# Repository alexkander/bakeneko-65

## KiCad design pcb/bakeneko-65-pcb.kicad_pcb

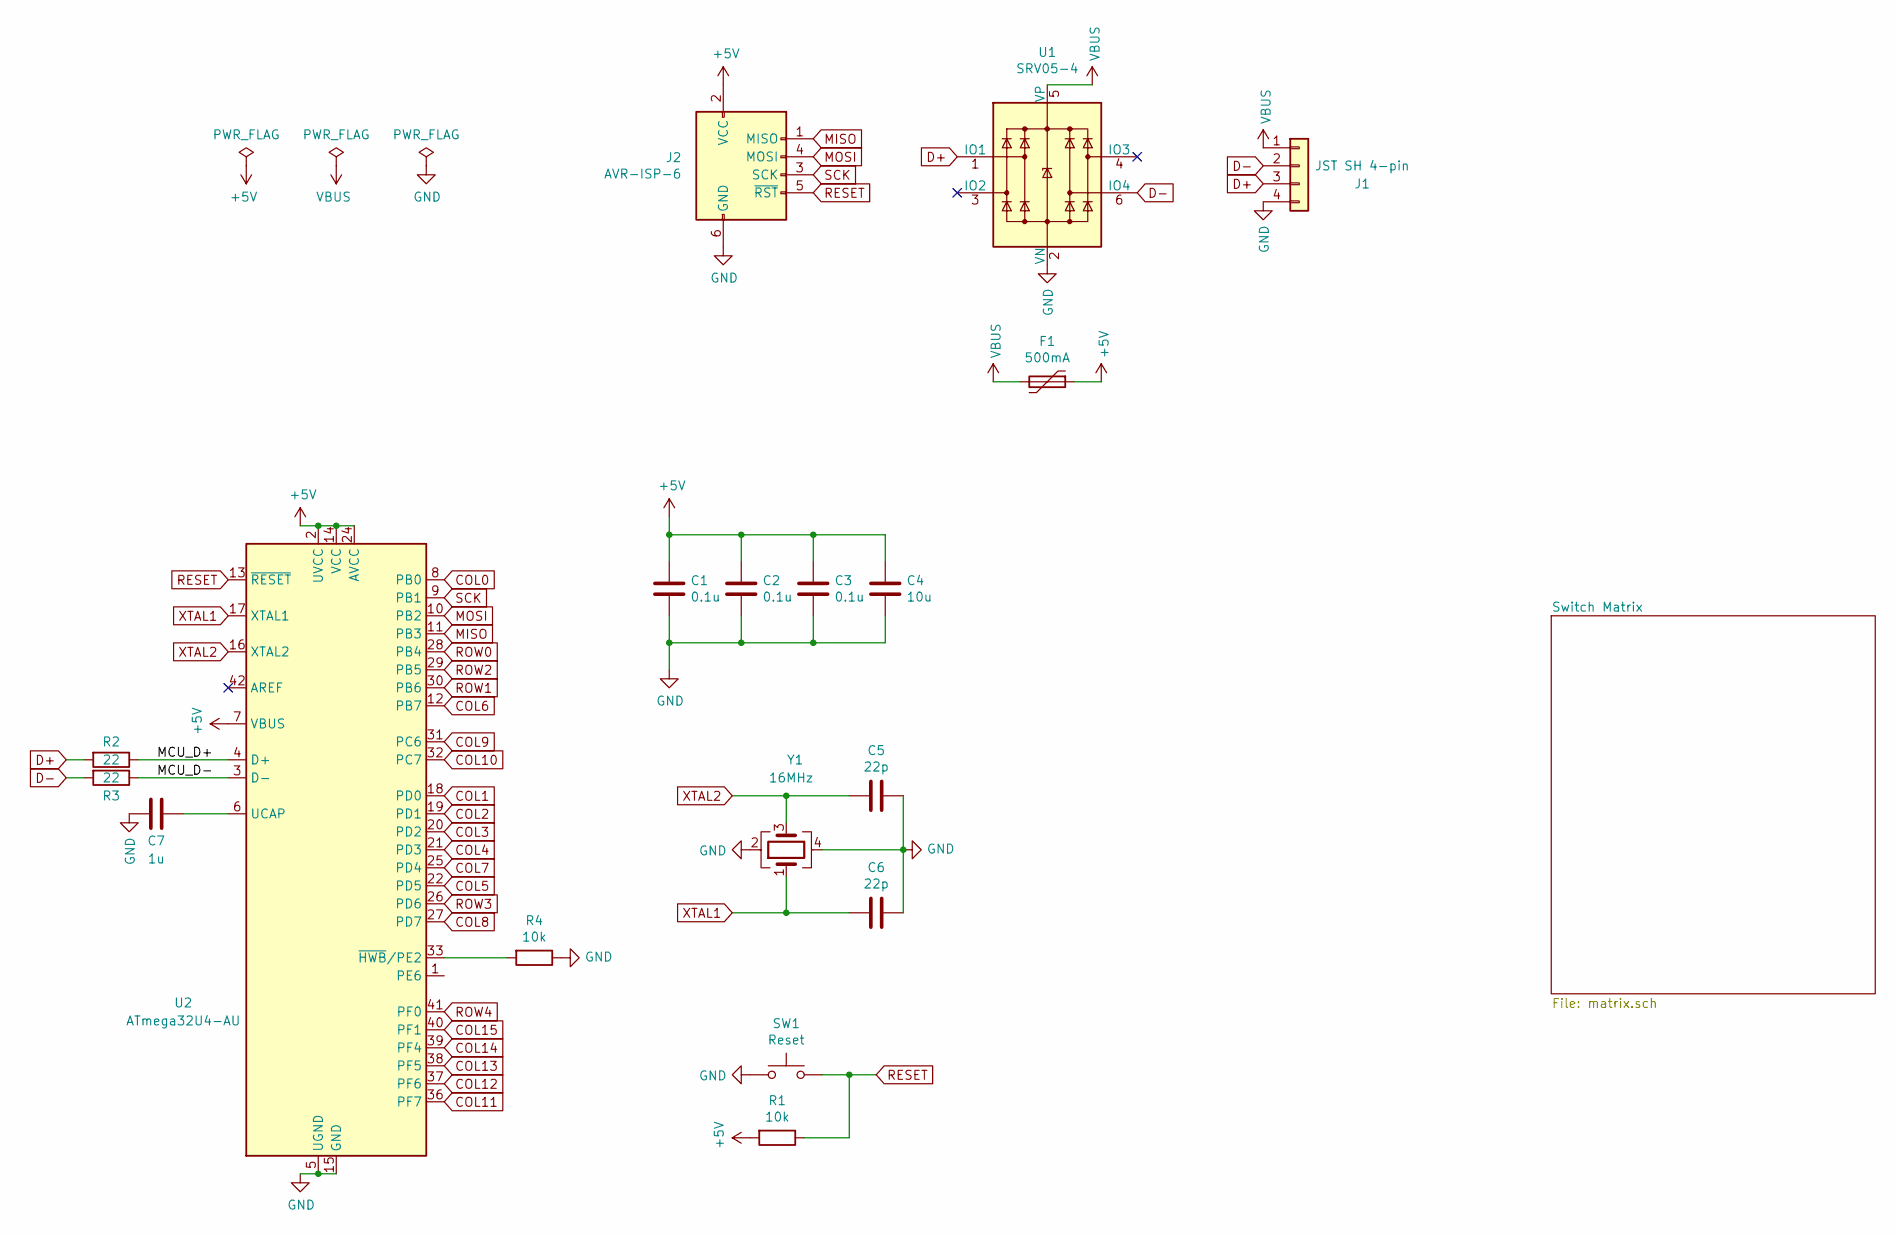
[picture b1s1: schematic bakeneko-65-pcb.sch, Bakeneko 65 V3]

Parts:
C1, C2, C3: 0.1u; C_0805_2012Metric; LCSC Part # C49678
C4: 10u; C_0805_2012Metric; LCSC Part # C15850
C5, C6: 22p; C_0805_2012Metric; LCSC Part # C1804
C7: 1u; C_0805_2012Metric; LCSC Part # C28323
F1: 500mA; Fuse_1206_3216Metric; LCSC Part # C70076
J1: JST SH 4-pin; JST_SH_SM04B-SRSS-TB_1x04-1MP_P1.00mm_Horizontal; LCSC Part # C160404
J2: AVR-ISP-6; Reset_Pretty
R1, R4: 10k; R_0805_2012Metric; LCSC Part # C17414
R2, R3: 22; R_0805_2012Metric; LCSC Part # C17561
SW1: Reset; SW_SPST_TL3342; LCSC Part # C318884
U1: SRV05-4; SOT-23-6; LCSC Part # C85364
U2: ATmega32U4-AU; TQFP-44_10x10mm_P0.8mm; LCSC Part # C44854
Y1: 16MHz; Crystal_SMD_3225-4Pin_3.2x2.5mm; LCSC Part # C13738

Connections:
+5V: C1.1, C2.1, C3.1, C4.1, F1.1, J2.2 (VCC), R1.2, U2.2 (UVCC), U2.7 (VBUS), U2.14 (VCC), U2.24 (AVCC), U2.34 (VCC), U2.44 (AVCC)
/MCU_D+: R2.1, U2.4 (D+)
/MCU_D-: R3.1, U2.3 (D-)
COL0: U2.8 (PB0); also elsewhere on the board
COL1: U2.18 (PD0); also elsewhere on the board
COL2: U2.19 (PD1); also elsewhere on the board
COL3: U2.20 (PD2); also elsewhere on the board
COL4: U2.21 (PD3); also elsewhere on the board
COL5: U2.22 (PD5); also elsewhere on the board
COL6: U2.12 (PB7); also elsewhere on the board
COL7: U2.25 (PD4); also elsewhere on the board
COL8: U2.27 (PD7); also elsewhere on the board
COL9: U2.31 (PC6); also elsewhere on the board
COL10: U2.32 (PC7); also elsewhere on the board
COL11: U2.36 (PF7); also elsewhere on the board
COL12: U2.37 (PF6); also elsewhere on the board
COL13: U2.38 (PF5); also elsewhere on the board
COL14: U2.39 (PF4); also elsewhere on the board
COL15: U2.40 (PF1); also elsewhere on the board
D+: J1.3, R2.2, U1.1 (IO1)
D-: J1.2, R3.2, U1.6 (IO4)
GND: C1.2, C2.2, C3.2, C4.2, C5.1, C6.1, C7.2, J1.4, J2.6 (GND), R4.1, SW1.1, U1.2 (VN), U2.5 (UGND), U2.15 (GND), U2.23 (GND), U2.35 (GND), U2.43 (GND), Y1.2, Y1.4
MISO: J2.1 (MISO), U2.11 (PB3)
MOSI: J2.4 (MOSI), U2.10 (PB2)
unnamed: C7.1, U2.6 (UCAP)
unnamed: R4.2, U2.33 (~HWB~/PE2)
RESET: J2.5 (~RST), R1.1, SW1.2, U2.13 (~RESET)
ROW0: U2.28 (PB4); also elsewhere on the board
ROW1: U2.30 (PB6); also elsewhere on the board
ROW2: U2.29 (PB5); also elsewhere on the board
ROW3: U2.26 (PD6); also elsewhere on the board
ROW4: U2.41 (PF0); also elsewhere on the board
SCK: J2.3 (SCK), U2.9 (PB1)
VBUS: F1.2, J1.1, U1.5 (VP)
XTAL1: C6.2, U2.17 (XTAL1), Y1.1
XTAL2: C5.2, U2.16 (XTAL2), Y1.3

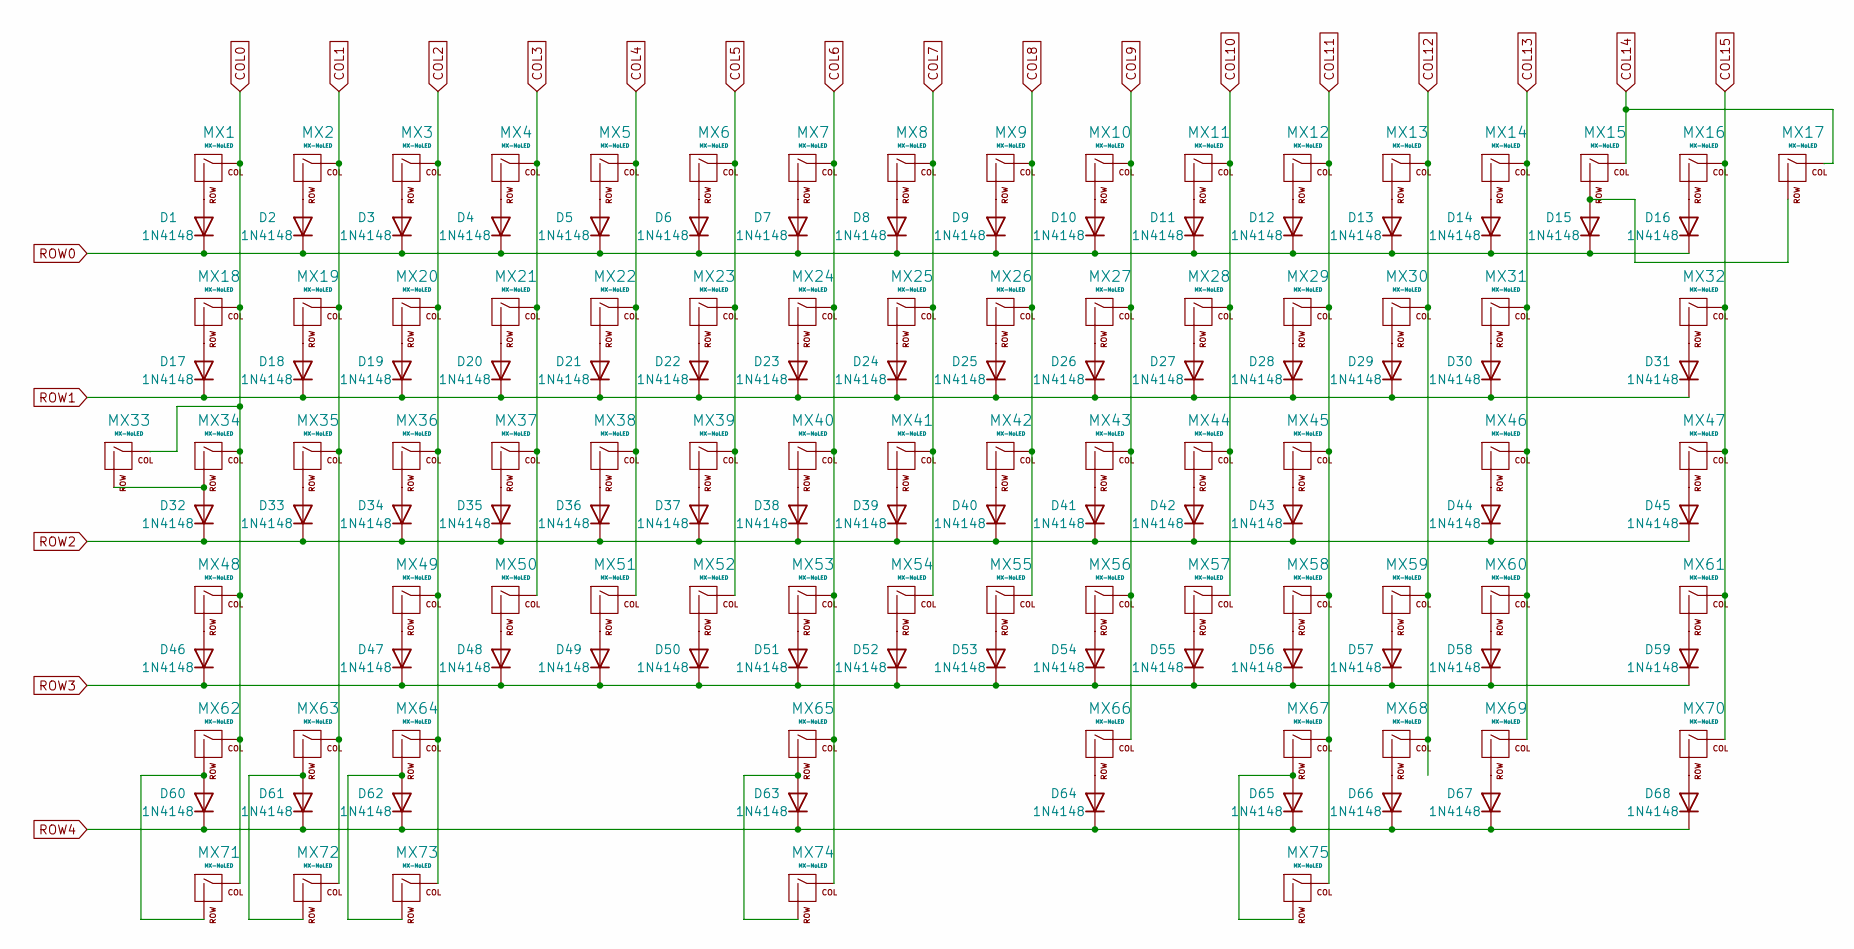
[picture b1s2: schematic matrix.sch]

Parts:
D1, D2, D3, D4, D5, D6, D7, D8, D9, D10, D11, D12, D13, D14, D15, D16, D17, D18, D19, D20, D21, D22, D23, D24, D25, D26, D27, D28, D29, D30, D31, D32, D33, D34, D35, D36, D37, D38, D39, D40, D41, D42, D43, D44, D45, D46, D47, D48, D49, D50, D51, D52, D53, D54, D55, D56, D57, D58, D59, D60, D61, D62, D63, D64, D65, D66, D67, D68: 1N4148; D_SOD-123; LCSC Part # C81598
MX1, MX2, MX3, MX4, MX5, MX6, MX7, MX8, MX9, MX10, MX11, MX12, MX13, MX14, MX15, MX16, MX17, MX18, MX19, MX20, MX21, MX22, MX23, MX24, MX25, MX26, MX27, MX28, MX29, MX30, MX31, MX32, MX33, MX34, MX35, MX36, MX37, MX38, MX39, MX40, MX41, MX42, MX43, MX44, MX45, MX46, MX47, MX48, MX49, MX50, MX51, MX52, MX53, MX54, MX55, MX56, MX57, MX58, MX59, MX60, MX61, MX62, MX63, MX64, MX65, MX66, MX67, MX68, MX69, MX70, MX71, MX72, MX73, MX74, MX75: MX-NoLED; CherryMX_Hotswap

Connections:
COL0: MX1.1 (COL), MX18.1 (COL), MX33.1 (COL), MX34.1 (COL), MX48.1 (COL), MX62.1 (COL), MX71.1 (COL); also elsewhere on the board
COL1: MX2.1 (COL), MX19.1 (COL), MX35.1 (COL), MX63.1 (COL), MX72.1 (COL); also elsewhere on the board
COL2: MX3.1 (COL), MX20.1 (COL), MX36.1 (COL), MX49.1 (COL), MX64.1 (COL), MX73.1 (COL); also elsewhere on the board
COL3: MX4.1 (COL), MX21.1 (COL), MX37.1 (COL), MX50.1 (COL); also elsewhere on the board
COL4: MX5.1 (COL), MX22.1 (COL), MX38.1 (COL), MX51.1 (COL); also elsewhere on the board
COL5: MX6.1 (COL), MX23.1 (COL), MX39.1 (COL), MX52.1 (COL); also elsewhere on the board
COL6: MX7.1 (COL), MX24.1 (COL), MX40.1 (COL), MX53.1 (COL), MX65.1 (COL), MX74.1 (COL); also elsewhere on the board
COL7: MX8.1 (COL), MX25.1 (COL), MX41.1 (COL), MX54.1 (COL); also elsewhere on the board
COL8: MX9.1 (COL), MX26.1 (COL), MX42.1 (COL), MX55.1 (COL); also elsewhere on the board
COL9: MX10.1 (COL), MX27.1 (COL), MX43.1 (COL), MX56.1 (COL), MX66.1 (COL); also elsewhere on the board
COL10: MX11.1 (COL), MX28.1 (COL), MX44.1 (COL), MX57.1 (COL); also elsewhere on the board
COL11: MX12.1 (COL), MX29.1 (COL), MX45.1 (COL), MX58.1 (COL), MX67.1 (COL), MX75.1 (COL); also elsewhere on the board
COL12: MX13.1 (COL), MX30.1 (COL), MX59.1 (COL), MX68.1 (COL); also elsewhere on the board
COL13: MX14.1 (COL), MX31.1 (COL), MX46.1 (COL), MX60.1 (COL), MX69.1 (COL); also elsewhere on the board
COL14: MX15.1 (COL), MX17.1 (COL); also elsewhere on the board
COL15: MX16.1 (COL), MX32.1 (COL), MX47.1 (COL), MX61.1 (COL), MX70.1 (COL); also elsewhere on the board
unnamed: D1.2 (A), MX1.2 (ROW)
unnamed: D2.2 (A), MX2.2 (ROW)
unnamed: D3.2 (A), MX3.2 (ROW)
unnamed: D4.2 (A), MX4.2 (ROW)
unnamed: D5.2 (A), MX5.2 (ROW)
unnamed: D6.2 (A), MX6.2 (ROW)
unnamed: D7.2 (A), MX7.2 (ROW)
unnamed: D8.2 (A), MX8.2 (ROW)
unnamed: D9.2 (A), MX9.2 (ROW)
unnamed: D10.2 (A), MX10.2 (ROW)
unnamed: D11.2 (A), MX11.2 (ROW)
unnamed: D12.2 (A), MX12.2 (ROW)
unnamed: D13.2 (A), MX13.2 (ROW)
unnamed: D14.2 (A), MX14.2 (ROW)
unnamed: D15.2 (A), MX15.2 (ROW), MX17.2 (ROW)
unnamed: D16.2 (A), MX16.2 (ROW)
unnamed: D17.2 (A), MX18.2 (ROW)
unnamed: D18.2 (A), MX19.2 (ROW)
unnamed: D19.2 (A), MX20.2 (ROW)
unnamed: D20.2 (A), MX21.2 (ROW)
unnamed: D21.2 (A), MX22.2 (ROW)
unnamed: D22.2 (A), MX23.2 (ROW)
unnamed: D23.2 (A), MX24.2 (ROW)
unnamed: D24.2 (A), MX25.2 (ROW)
unnamed: D25.2 (A), MX26.2 (ROW)
unnamed: D26.2 (A), MX27.2 (ROW)
unnamed: D27.2 (A), MX28.2 (ROW)
unnamed: D28.2 (A), MX29.2 (ROW)
unnamed: D29.2 (A), MX30.2 (ROW)
unnamed: D30.2 (A), MX31.2 (ROW)
unnamed: D31.2 (A), MX32.2 (ROW)
unnamed: D32.2 (A), MX33.2 (ROW), MX34.2 (ROW)
unnamed: D33.2 (A), MX35.2 (ROW)
unnamed: D34.2 (A), MX36.2 (ROW)
unnamed: D35.2 (A), MX37.2 (ROW)
unnamed: D36.2 (A), MX38.2 (ROW)
unnamed: D37.2 (A), MX39.2 (ROW)
unnamed: D38.2 (A), MX40.2 (ROW)
unnamed: D39.2 (A), MX41.2 (ROW)
unnamed: D40.2 (A), MX42.2 (ROW)
unnamed: D41.2 (A), MX43.2 (ROW)
unnamed: D42.2 (A), MX44.2 (ROW)
unnamed: D43.2 (A), MX45.2 (ROW)
unnamed: D44.2 (A), MX46.2 (ROW)
unnamed: D45.2 (A), MX47.2 (ROW)
unnamed: D46.2 (A), MX48.2 (ROW)
unnamed: D47.2 (A), MX49.2 (ROW)
unnamed: D48.2 (A), MX50.2 (ROW)
unnamed: D49.2 (A), MX51.2 (ROW)
unnamed: D50.2 (A), MX52.2 (ROW)
unnamed: D51.2 (A), MX53.2 (ROW)
unnamed: D52.2 (A), MX54.2 (ROW)
unnamed: D53.2 (A), MX55.2 (ROW)
unnamed: D54.2 (A), MX56.2 (ROW)
unnamed: D55.2 (A), MX57.2 (ROW)
unnamed: D56.2 (A), MX58.2 (ROW)
unnamed: D57.2 (A), MX59.2 (ROW)
unnamed: D58.2 (A), MX60.2 (ROW)
unnamed: D59.2 (A), MX61.2 (ROW)
unnamed: D60.2 (A), MX62.2 (ROW), MX71.2 (ROW)
unnamed: D61.2 (A), MX63.2 (ROW), MX72.2 (ROW)
unnamed: D62.2 (A), MX64.2 (ROW), MX73.2 (ROW)
unnamed: D63.2 (A), MX65.2 (ROW), MX74.2 (ROW)
unnamed: D64.2 (A), MX66.2 (ROW)
unnamed: D65.2 (A), MX67.2 (ROW), MX75.2 (ROW)
unnamed: D66.2 (A), MX68.2 (ROW)
unnamed: D67.2 (A), MX69.2 (ROW)
unnamed: D68.2 (A), MX70.2 (ROW)
ROW0: D1.1 (K), D2.1 (K), D3.1 (K), D4.1 (K), D5.1 (K), D6.1 (K), D7.1 (K), D8.1 (K), D9.1 (K), D10.1 (K), D11.1 (K), D12.1 (K), D13.1 (K), D14.1 (K), D15.1 (K), D16.1 (K); also elsewhere on the board
ROW1: D17.1 (K), D18.1 (K), D19.1 (K), D20.1 (K), D21.1 (K), D22.1 (K), D23.1 (K), D24.1 (K), D25.1 (K), D26.1 (K), D27.1 (K), D28.1 (K), D29.1 (K), D30.1 (K), D31.1 (K); also elsewhere on the board
ROW2: D32.1 (K), D33.1 (K), D34.1 (K), D35.1 (K), D36.1 (K), D37.1 (K), D38.1 (K), D39.1 (K), D40.1 (K), D41.1 (K), D42.1 (K), D43.1 (K), D44.1 (K), D45.1 (K); also elsewhere on the board
ROW3: D46.1 (K), D47.1 (K), D48.1 (K), D49.1 (K), D50.1 (K), D51.1 (K), D52.1 (K), D53.1 (K), D54.1 (K), D55.1 (K), D56.1 (K), D57.1 (K), D58.1 (K), D59.1 (K); also elsewhere on the board
ROW4: D60.1 (K), D61.1 (K), D62.1 (K), D63.1 (K), D64.1 (K), D65.1 (K), D66.1 (K), D67.1 (K), D68.1 (K); also elsewhere on the board

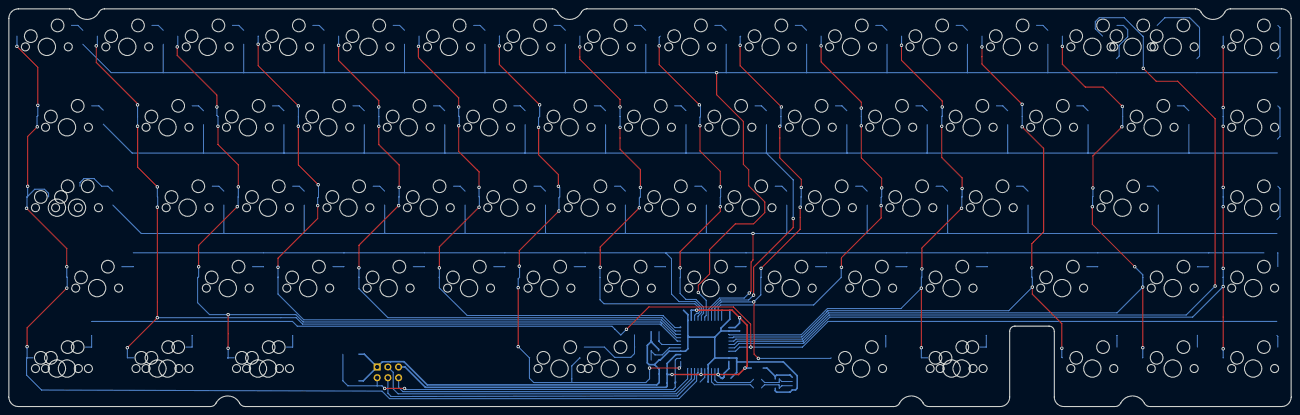
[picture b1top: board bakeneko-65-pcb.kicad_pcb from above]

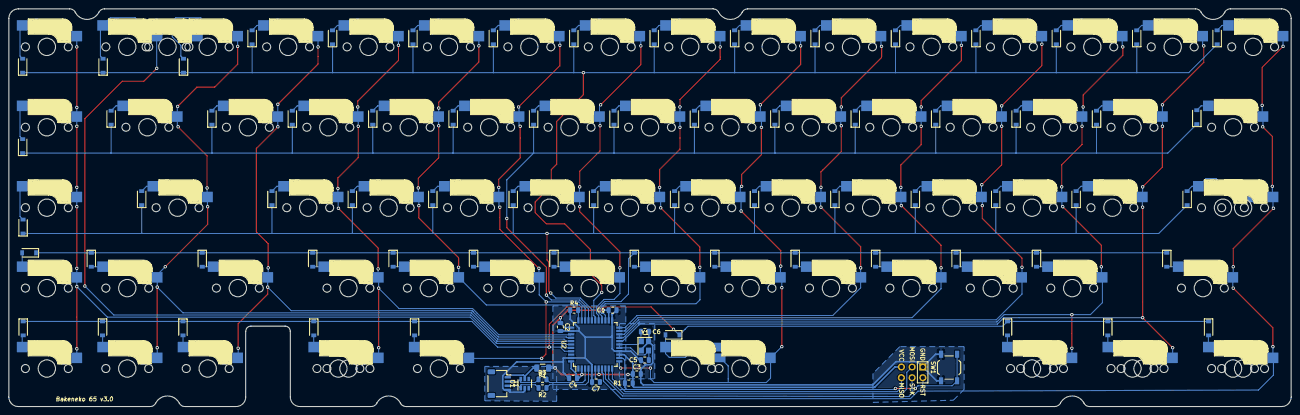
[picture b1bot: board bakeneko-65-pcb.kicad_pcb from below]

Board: 2 copper layers, 303.8 x 94.2 mm, 161 parts (86 on the bottom side), 104 nets.

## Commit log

2021-08-24 agrega sockets
